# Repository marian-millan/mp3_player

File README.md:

<div align="center">

# Portable MP3 Player

### A custom, distraction-free music player inspired by retro physical media

**KiCad 9 · Arduino · DFPlayer Mini · SSD1306 OLED**

</div>

## Overview

We love music, but wanted a way to listen without constantly reaching for a
phone and getting distracted. Inspired by the tactile feel of retro physical
media, we set out to build a dedicated hardware MP3 player.

This repository contains versioned hardware designs, assembled-board models,
and Arduino firmware. The player combines physical transport controls and a
rotary volume encoder with a compact OLED interface.

## Features

- Standalone MP3 playback through a DFRobot DFPlayer Mini
- 128 × 64 SSD1306 OLED interface
- Previous, play/pause, and next track buttons
- Rotary encoder volume control
- Custom KiCad schematic and two-layer PCB layout
- STEP model of the assembled board

## Repository Layout

| Path | Contents |
| --- | --- |
| [`versions/v1/firmware`](versions/v1/firmware) | Version 1 Arduino firmware |
| [`versions/v1/hardware/mp3_player_schematic_v1.kicad_sch`](versions/v1/hardware/mp3_player_schematic_v1.kicad_sch) | Version 1 KiCad schematic |
| [`versions/v1/hardware/mp3_player_pcb_v1.kicad_pcb`](versions/v1/hardware/mp3_player_pcb_v1.kicad_pcb) | Version 1 KiCad PCB layout |
| [`versions/v1/hardware/mp3_player_assembly_v1.step`](versions/v1/hardware/mp3_player_assembly_v1.step) | Version 1 assembled-board model |
| [`versions/v2`](versions/v2) | Version 2 placeholder—in development |

```text
versions/
├── v1/
│   ├── firmware/
│   │   └── mp3_player_v1/
│   │       └── mp3_player_v1.ino
│   └── hardware/
│       ├── mp3_player_assembly_v1.step
│       ├── mp3_player_pcb_v1.kicad_pcb
│       └── mp3_player_schematic_v1.kicad_sch
└── v2/
    └── README.md
```

### Versioning Convention

Each release keeps its firmware and hardware together under
`versions/v<release>`. Project artifacts follow the
`descriptive_name_v<release>.<extension>` naming pattern.

New iterations should be added as sibling directories rather than overwriting
earlier versions. Arduino sketches are kept in matching directories because
the Arduino IDE expects a sketch and its containing directory to share a name.

## Firmware

### Requirements

- Arduino IDE or Arduino CLI
- An Arduino-compatible board configured for the project hardware
- [DFRobotDFPlayerMini](https://github.com/DFRobot/DFRobotDFPlayerMini)
- [U8g2](https://github.com/olikraus/u8g2)

`SoftwareSerial`, `SPI`, and `Wire` are supplied by the Arduino platform.

### Pin Map

| Function | Pin |
| --- | ---: |
| Previous track button | D2 |
| Play/pause button | D3 |
| Next track button | D4 |
| Rotary encoder A | D8 |
| Rotary encoder B | D9 |
| DFPlayer serial | D10 / D11 |
| OLED display | Hardware I²C |

The buttons use the microcontroller's internal pull-up resistors and are active
low. Playback actions occur when a button is released.

### Upload

1. Install the `DFRobotDFPlayerMini` and `U8g2` libraries with the Arduino
   Library Manager.
2. Open
   [`versions/v1/firmware/mp3_player_v1/mp3_player_v1.ino`](versions/v1/firmware/mp3_player_v1/mp3_player_v1.ino).
3. Select the correct board and serial port.
4. Compile and upload the sketch.
5. Insert a prepared microSD card into the DFPlayer Mini and power the player.

On startup, the firmware initializes the display, sets the volume to `20`, and
starts the first track. The current interface labels tracks as
`trackNNN.mp3` using the file number reported by the DFPlayer.

## Current Status

Version 1 includes the complete design sources and an initial working firmware
implementation. The firmware currently focuses on core playback, volume
control, and a minimal track-number interface; metadata browsing and richer
error reporting are not yet implemented.

Version 2 is currently in development. Its directory is reserved, but no
hardware or firmware artifacts have been published yet.

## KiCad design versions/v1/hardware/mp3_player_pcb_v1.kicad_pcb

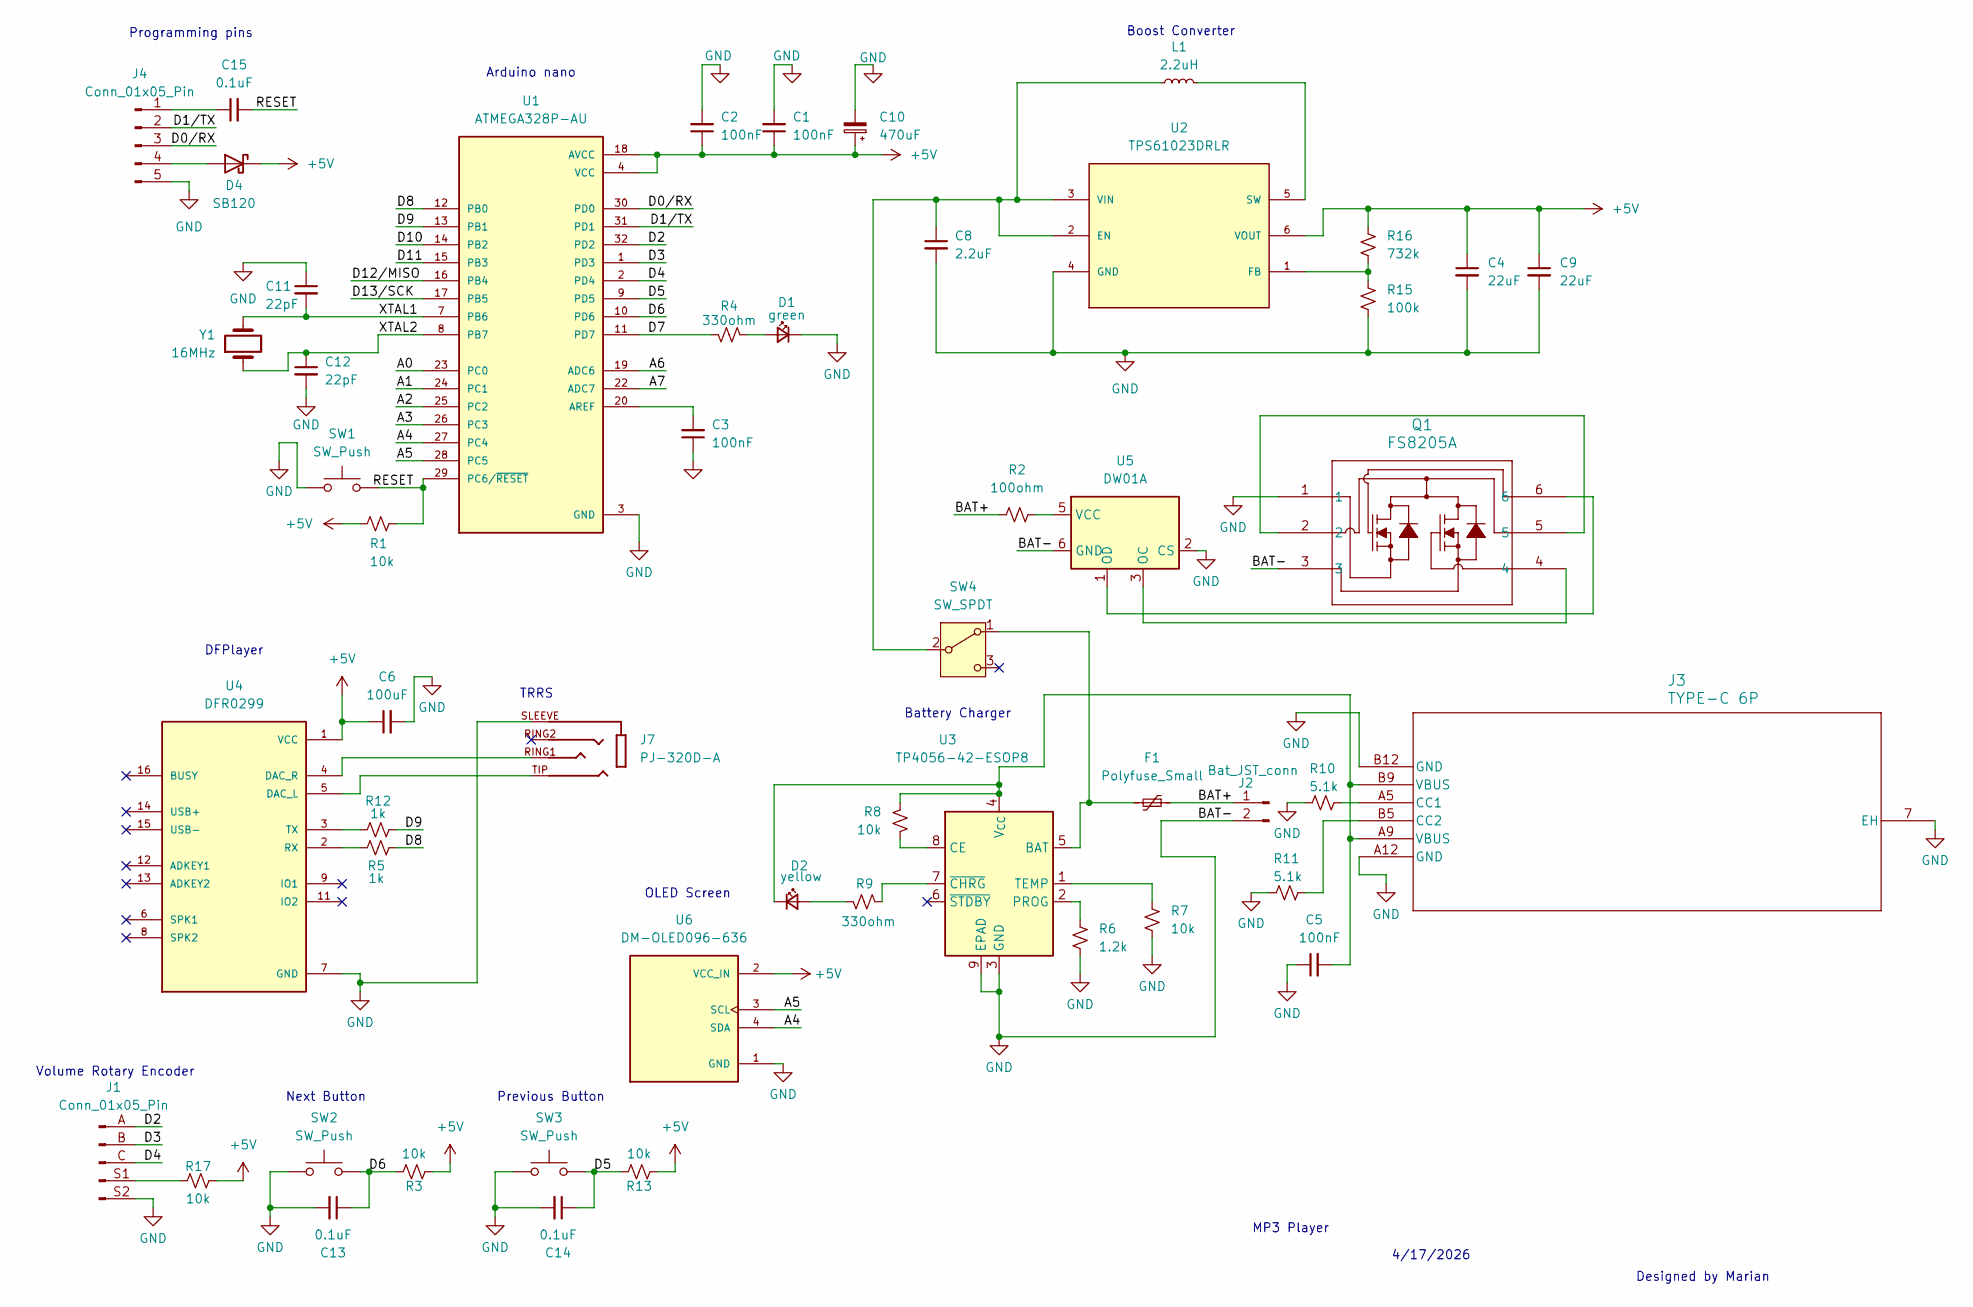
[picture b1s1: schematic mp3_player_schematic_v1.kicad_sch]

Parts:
C1, C2, C3, C5: 100nF; C_0603_1608Metric
C4, C9: 22uF; C_0603_1608Metric
C6: 100uF; C_0603_1608Metric
C8: 2.2uF; C_0603_1608Metric
C10: 470uF; CAP-SMD_BD6.3-L6.6-W6.6-FD
C11, C12: 22pF; C_0603_1608Metric
C13, C14, C15: 0.1uF; C_0603_1608Metric
D1: green; LED_0805_2012Metric
D2: yellow; LED_0805_2012Metric
D4: SB120; D_0805_2012Metric
F1: Polyfuse_Small; Fuse_0805_2012Metric
J1: Conn_01x05_Pin; rotary_encoder_socket_pads
J2: Bat_JST_conn; JST_PH_B2B-PH-K_1x02_P2.00mm_Vertical
J3: TYPE-C 6P; CONN_TYPE-C-6P_SHN
J4: Conn_01x05_Pin; PinHeader_1x05_P2.54mm_Vertical
J7: PJ-320D-A; HRO_PJ-320D-A; PARTREV B
L1: 2.2uH; IND-SMD_L4.9-W4.5
Q1: FS8205A; FS2805
R1, R3, R7, R8, R13, R17: 10k; R_0603_1608Metric
R2: 100ohm; R_0603_1608Metric
R4, R9: 330ohm; R_0603_1608Metric
R5, R12: 1k; R_0603_1608Metric
R6: 1.2k; R_0603_1608Metric
R10, R11: 5.1k; R_0603_1608Metric
R15: 100k; R_0603_1608Metric
R16: 732k; R_0603_1608Metric
SW1: SW_Push; SW_Push_SPST_NO_Alps_SKRK
SW2, SW3: SW_Push; pushbutton
SW4: SW_SPDT; SW-SMD_MST-12D18G4-SPDT-SLIDE-SWITCH
U1: ATMEGA328P-AU; ATPMEGA328P; PARTREV 8271A
U2: TPS61023DRLR; MANUFACTURER_PART_NUMBER TPS61023DRLR
U3: TP4056-42-ESOP8; SOIC-8-1EP_3.9x4.9mm_P1.27mm_EP2.41x3.3mm_ThermalVias
U4: DFR0299; MODULE_DFR0299
U5: DW01A; SOT-23-6
U6: DM-OLED096-636; OLED_screen; PARTREV 2018-09-10
Y1: 16MHz; XTAL_X49SM_S2_YXC

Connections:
+5V: C1.1, C2.1, C4.1, C6.1, C9.1, C10.1, D4.1 (K), R1.1, R3.2, R13.2, R16.1, R17.1, U1.4 (VCC), U1.6 (VCC), U1.18 (AVCC), U2.6 (VOUT), U4.1 (VCC), U6.2 (VCC_IN)
/A0: U1.23 (PC0)
/A1: U1.24 (PC1)
/A2: U1.25 (PC2)
/A3: U1.26 (PC3)
/A4: U1.27 (PC4), U6.4 (SDA)
/A5: U1.28 (PC5), U6.3 (SCL)
/A6: U1.19 (ADC6)
/A7: U1.22 (ADC7)
/BAT+: F1.1, J2.1, R2.1
/D0/RX: J4.3, U1.30 (PD0)
/D1/TX: J4.2, U1.31 (PD1)
/D2: J1.A (Pin_1), U1.32 (PD2)
/D3: J1.B (Pin_2), U1.1 (PD3)
/D4: J1.C (Pin_3), U1.2 (PD4)
/D5: C14.1, R13.1, SW3.2, U1.9 (PD5)
/D6: C13.1, R3.1, SW2.2, U1.10 (PD6)
/D7: R4.2, U1.11 (PD7)
/D8: R5.2, U1.12 (PB0)
/D9: R12.2, U1.13 (PB1)
/D10: U1.14 (PB2)
/D11: U1.15 (PB3)
/D12/MISO: U1.16 (PB4)
/D13/SCK: U1.17 (PB5)
/RESET: C15.2, R1.2, SW1.2, U1.29 (PC6/~RESET)
/XTAL1: C11.2, U1.7 (PB6), Y1.2
/XTAL2: C12.1, U1.8 (PB7), Y1.1
GND: C1.2, C2.2, C3.1, C4.2, C5.1, C6.2, C8.2, C9.2, C10.2, C11.1, C12.2, C13.2, C14.2, D1.1 (K), J1.S2 (Pin_5), J2.2, J3.7 (EH), J3.A12 (GND), J3.B12 (GND), J4.5, J7.SLEEVE, Q1.1, Q1.3, R6.2, R7.2, R10.2, R11.2, R15.2, SW1.1, SW2.1, SW3.1, U1.3 (GND), U1.5 (GND), U1.21 (GND), U2.4 (GND), U3.3 (GND), U3.9 (EPAD), U4.7 (GND), U4.10 (GND), U5.2 (CS), U5.6 (GND), U6.1 (GND)
unnamed: D1.2 (A), R4.1
unnamed: D2.2 (A), R9.2
unnamed: C5.2, D2.1 (K), J3.A9 (VBUS), J3.B9 (VBUS), R8.1, U3.4 (V_{CC})
unnamed: D4.2 (A), J4.4
unnamed: J1.S1 (Pin_4), R17.2
unnamed: J3.A5 (CC1), R10.1
unnamed: J3.B5 (CC2), R11.1
unnamed: C15.1, J4.1
unnamed: Q1.2, Q1.5
unnamed: F1.2, SW4.1 (A), U3.5 (BAT)
unnamed: C8.1, L1.1, SW4.2 (B), U2.2 (EN), U2.3 (VIN)
unnamed: C3.2, U1.20 (AREF)
unnamed: R15.1, R16.2, U2.1 (FB)
unnamed: L1.2, U2.5 (SW)
unnamed: R8.2, U3.8 (CE)
unnamed: R6.1, U3.2 (PROG)
unnamed: R7.1, U3.1 (TEMP)
unnamed: R9.1, U3.7 (~CHRG)
unnamed: J7.TIP, U4.5 (DAC_L)
unnamed: J7.RING1, U4.4 (DAC_R)
unnamed: R5.1, U4.2 (RX)
unnamed: R12.1, U4.3 (TX)
unnamed: Q1.4, U5.3 (OC)
unnamed: Q1.6, U5.1 (OD)
unnamed: R2.2, U5.5 (VCC)

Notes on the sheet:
4/17/2026
Previous Button
Programming pins
MP3 Player
Boost Converter
OLED Screen
Next Button
Arduino nano
Designed by Marian
Battery Charger
Volume Rotary Encoder
DFPlayer
TRRS

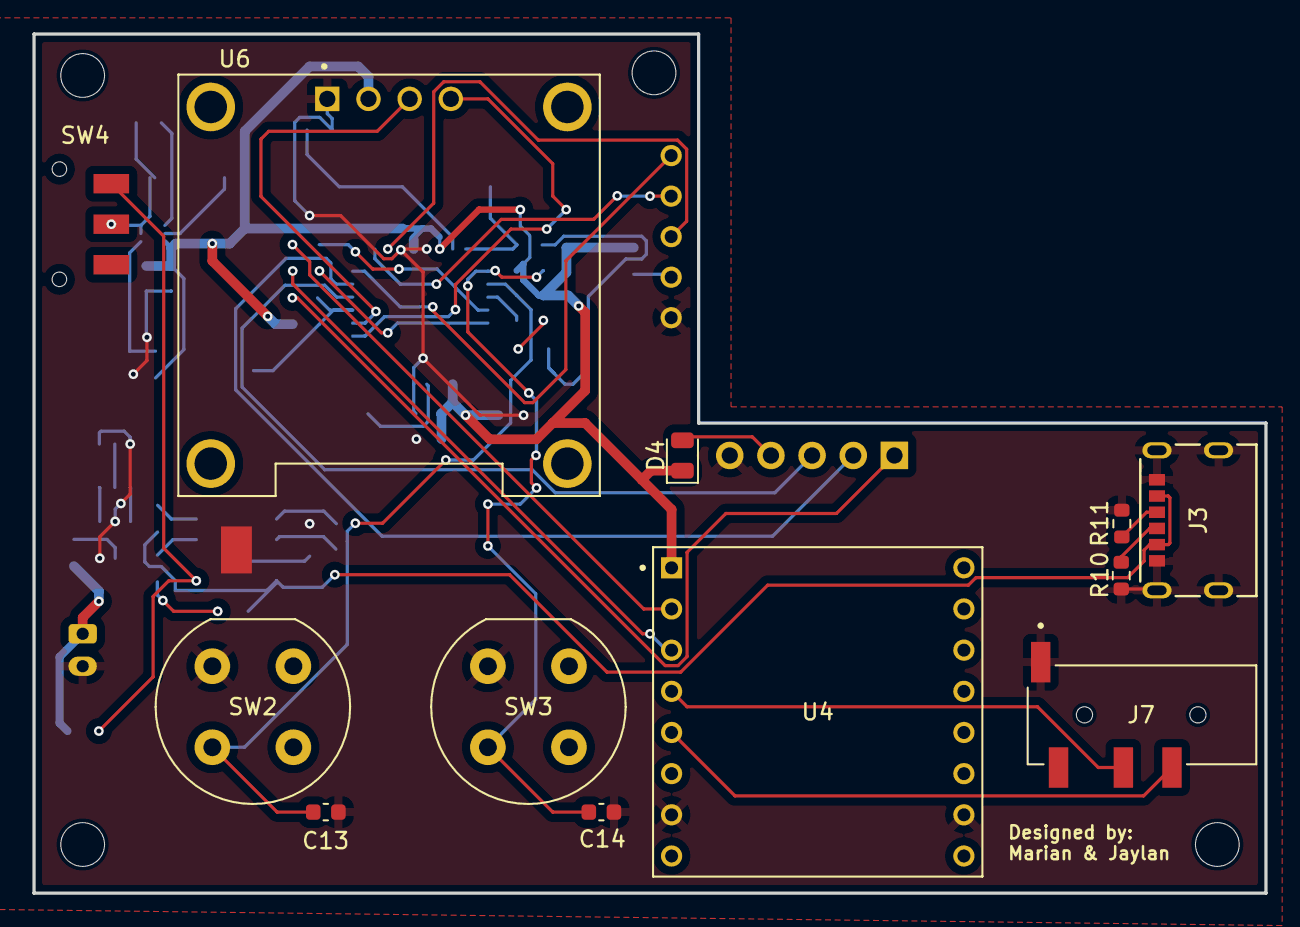
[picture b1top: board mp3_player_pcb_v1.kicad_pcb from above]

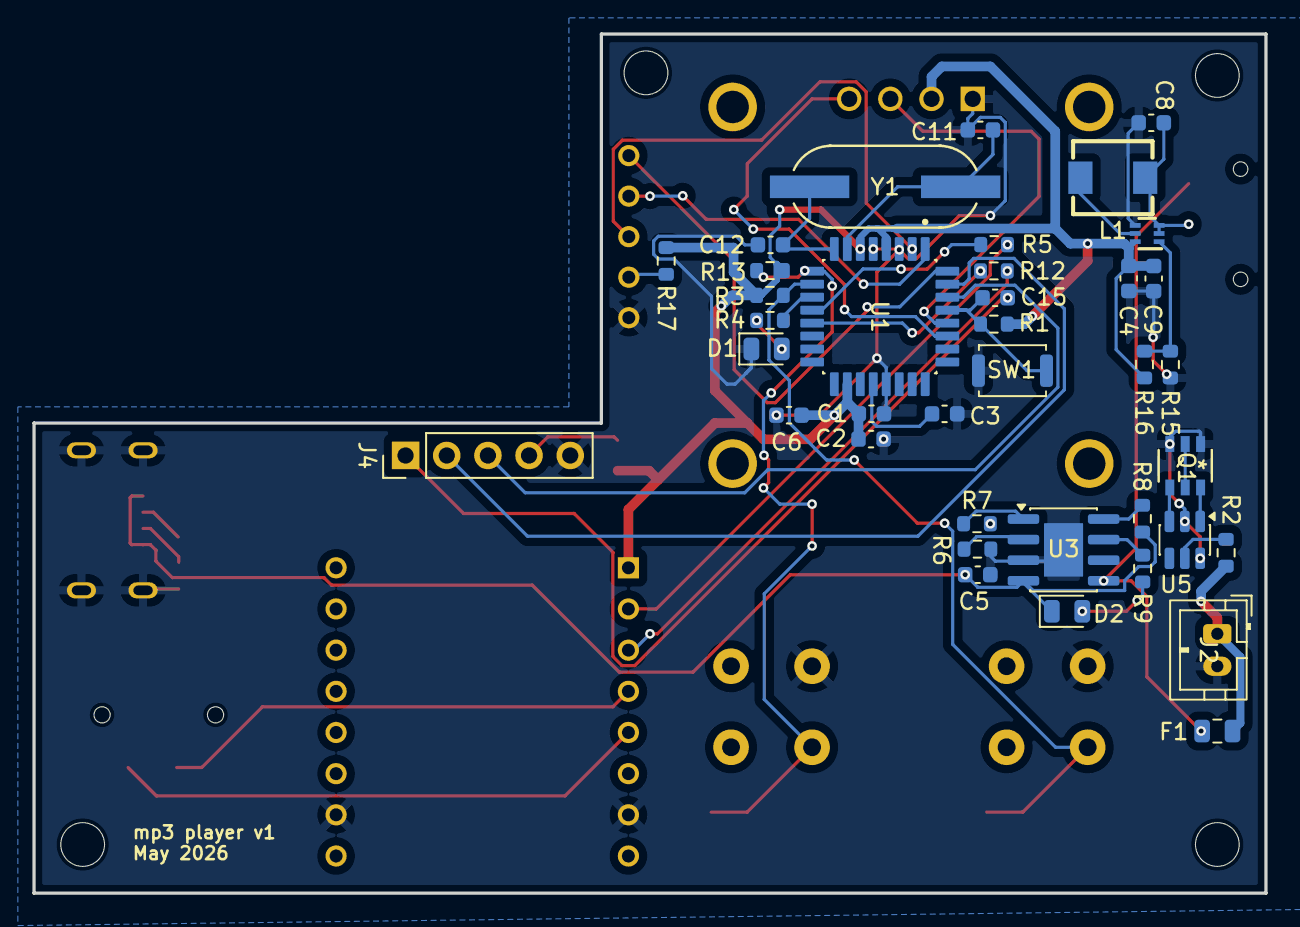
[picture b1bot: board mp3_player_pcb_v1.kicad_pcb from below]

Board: 2 copper layers, 76.0 x 53.0 mm, 51 parts (38 on the bottom side), 43 nets.

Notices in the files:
parts and their libraries:
COPYRIGHT: Copyright (C) 2022 Ultra Librarian. All rights reserved.
